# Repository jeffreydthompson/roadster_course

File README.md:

# Open Roadster

An open source remote control car you can build from scratch. The chassis, circuit board, firmware, and phone app are all here.

## What's inside

| | Folder | What you'll find |
|---|---|---|
| **Mechanical** | [`mechanical/`](mechanical/) | Chassis, steering and wheels in FreeCAD, ready-to-print STLs, a sheet metal base, and a Blender body |
| **Circuits** | [`circuits/`](circuits/) | A 4-layer ESP32-S3 controller board in KiCad, with order-ready files for JLCPCB |
| **Firmware** | [`code/firmware/`](code/firmware/) | Arduino firmware for motors, steering, lights, battery monitoring and Bluetooth LE |
| **App** | [`code/app/`](code/app/) | An iOS remote: tilt to steer, with throttle, gears, headlights and a fuel gauge |

Each folder has its own README with the details.

## The car at a glance

- **Brains:** ESP32-S3 on a custom 60 × 40 mm board
- **Drive:** two N20 gear motors, one per rear wheel
- **Steering:** micro servo with a steering linkage
- **Power:** single-cell LiPo, charged over USB-C, with a fuel gauge
- **Lights:** headlights, plus tail lights that double as brake lights
- **Control:** Bluetooth LE from your phone

## Building one

1. **Order the circuit board.** See [circuits](circuits/).
2. **Make the parts:** print the STLs, have the sheet metal base cut, and buy the motors, servo and bearings. See [mechanical](mechanical/).
3. **Flash the firmware** over USB-C. See [firmware](code/firmware/).
4. **Install the app** on your phone and drive. See [app](code/app/).

## Next steps

**A soft power switch.** Right now the car is turned on and off with a plain mechanical power switch. If it's left on, it keeps drawing current until the LiPo is run flat. Over-discharging a LiPo ruins it, and a damaged cell is a fire risk the next time it's charged.

The next board revision will add a soft switch: a push button that turns the car on, with power held on by the microcontroller. The firmware can then cut power completely, for example after a period of inactivity or when the battery gets low. That way the car can never be accidentally left on to drain the battery.

Other work in progress and known issues are tracked in [TODO.md](TODO.md).

## License

- Code (`code/`): [MIT](LICENSE)
- Hardware and mechanical designs (`mechanical/`, `circuits/`): [CC BY 4.0](https://creativecommons.org/licenses/by/4.0/)

See [LICENSE](LICENSE) for details.

The [Open Source Hardware logo](https://oshwa.org/resources/open-source-hardware-logo/) was designed by Macklin Chaffee and is used under a CC-SA license. Open Roadster is not OSHWA certified.

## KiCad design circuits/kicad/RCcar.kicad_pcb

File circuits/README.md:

# Circuits

The Open Roadster's controller: a 4-layer, 60 × 40 mm board built around an **ESP32-S3-MINI-1-N8**. It drives the motors, steering and lights, charges and monitors the battery, and talks to the phone over Bluetooth LE.

| Function | Part |
|---|---|
| Microcontroller (Wi-Fi + BLE) | ESP32-S3-MINI-1-N8 |
| Motor drivers (one per rear wheel) | 2× DRV8833 |
| Battery charger (single-cell LiPo, via USB-C) | MCP73831 |
| Fuel gauge | MAX17048 |
| 3.3 V supply (buck-boost) | TPS63001 |
| USB / battery power switchover | TPS2116 |
| USB-to-serial for programming | CP2102N |
| Connectors | USB-C, battery (PH2.0), 2× motor, servo, front + rear LED |

## What's here

```
circuits/
├── RCcar_schematic.pdf     # all schematic sheets, no software needed
├── kicad/                  # KiCad 10 project (schematic + PCB), where the design is maintained
├── fabrication/            # Gerbers, BOM, pick-and-place for JLCPCB (from KiCad)
└── easyeda/                # original EasyEDA Standard source (schematic + PCB)
    └── fabrication/        # archived order files exported from EasyEDA
```

- **Just looking?** Open `RCcar_schematic.pdf`. It has every sheet: Sheet 1, Power, Motor Control, LED Drivers, USB Programmer.
- **Editing the design?** Open `kicad/RCcar.kicad_pro` in [KiCad](https://www.kicad.org/) 10.
- **Ordering boards?** Use the files in `fabrication/` (see below).
- **Prefer EasyEDA?** In EasyEDA Standard, use **File → Open → EasyEDA Source** to open `easyeda/RCcar_schematic.json` and `easyeda/RCcar_pcb.json`.

## Ordering from JLCPCB

`fabrication/` has the order files in JLCPCB's format:

- `RCcar_kicad_gerber.zip`: upload this for bare boards (4 layers, 60 × 40 mm)
- `RCcar_bom_jlcpcb.csv` and `RCcar_cpl_jlcpcb.csv`: add these for assembly. Every part has an LCSC part number

Parts are on both sides, so choose two-sided assembly. Always check part rotations in JLCPCB's assembly preview before paying.

The original boards were made from the EasyEDA order files in `easyeda/fabrication/`, which are kept for reference. The KiCad set was checked against them:

- the same 91 parts with the same LCSC numbers
- identical positions, sides and rotations
- copper within about 1% per layer (pour edges)

KiCad also opens the solder mask around the bare mounting and locating holes.

## About the KiCad port

The design started in EasyEDA. The KiCad project was imported from the EasyEDA source and checked against it:

- Schematic and board agree on every connection. KiCad's schematic parity check finds no split or merged nets; the remaining parity notes are naming differences from the import.
- Design rules match EasyEDA's (0.152 mm minimum clearance, 0.254 mm tracks). DRC reports no clearance errors and no unconnected items.
- KiCad fills copper pours slightly differently from EasyEDA, so 14 short tracks (0.2 mm) were added where KiCad's fill couldn't reach a few fine-pitch pins that EasyEDA's pour connected (around U1, U3, U5, U6, U7 and R2).
- KiCad's Gerbers match EasyEDA's copper to within about 1% per layer. The differences are pour edges and thermal spokes around pads.
- The project is self-contained. All symbols and footprints live in project libraries (`RCcar.kicad_sym`, `RCcar.pretty/`), registered in the project's `sym-lib-table` and `fp-lib-table`.
- Remaining DRC/ERC items are left visible on purpose. They are cosmetic or come from the import:
  - courtyard overlaps from the tight placement
  - EasyEDA silkscreen touching pads
  - footprints that differ from their library copy by rounding or 3D model
  - EasyEDA symbols whose pin types trigger "not driven" and pin-type warnings
- 3D models aren't included yet, so the 3D viewer shows bare footprints.

The original EasyEDA board passes EasyEDA's design rule check with no errors, and all nets are routed.

## Known limitations

The board has no battery protection IC, so a pack left switched on can be run flat. See [TODO.md](../TODO.md) for the plan.

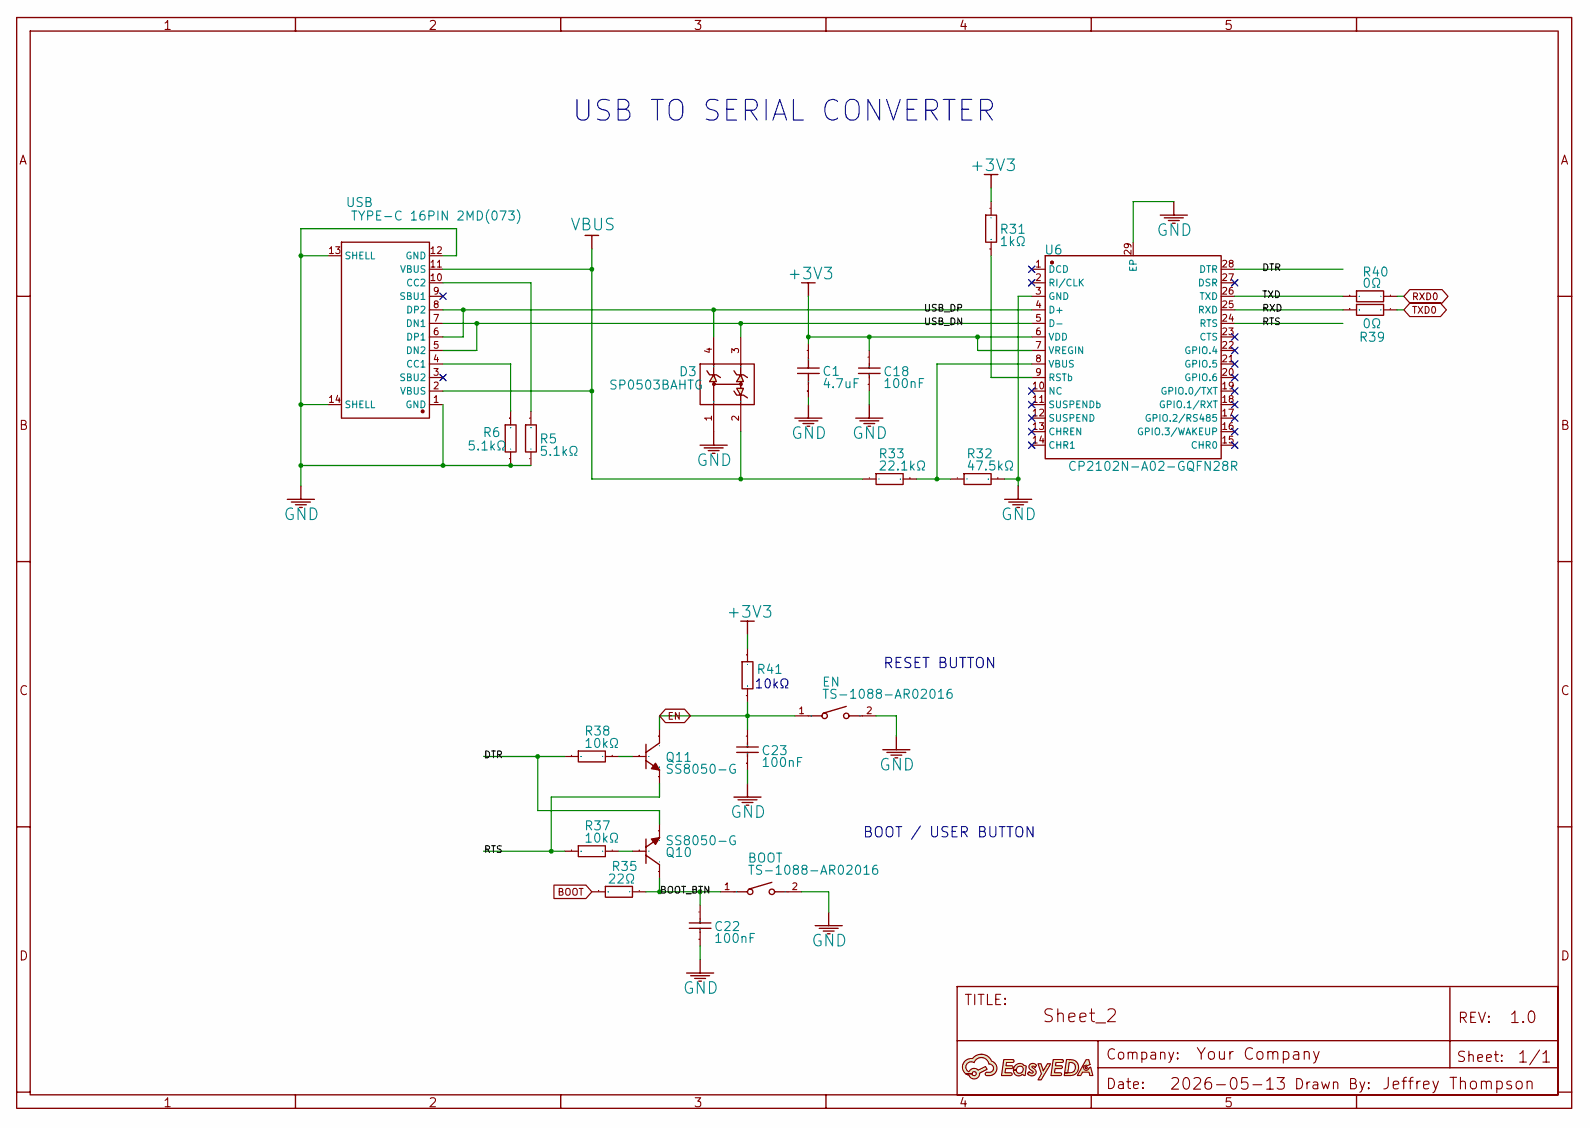
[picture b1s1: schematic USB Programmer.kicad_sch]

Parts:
A: A; Manufacturer Part ?
BOOT: TS-1088-AR02016; SW-SMD_L3.9-W3.0-P4.45; Manufacturer Part TS-1088-AR02016
C1: 4.7uF; C0402; Manufacturer Part CL05A475MP5NRNC
C18, C22, C23: 100nF; C0402_NEW; Manufacturer Part CL05B104KO5NNNC
D3: SP0503BAHTG; SOT-143_L2.9-W1.3-P1.92-LS2.3-BR; Manufacturer Part SP0503BAHTG
EN: TS-1088-AR02016; SW-SMD_L3.9-W3.0-P4.45; Manufacturer Part TS-1088-AR02016
Q10, Q11: SS8050-G; SOT-23-3_L2.9-W1.6-P1.90-LS2.8-BR; Manufacturer Part SS8050-G
R5, R6: 5.1kΩ; R0402; Manufacturer Part 0402WGF5101TCE
R31: 1kΩ; R0402; Manufacturer Part 0402WGF1001TCE
R32: 47.5kΩ; R0402; Manufacturer Part 0402WGF4752TCE
R33: 22.1kΩ; R0402; Manufacturer Part 0402WGF2212TCE
R35: 22Ω; R0402; Manufacturer Part 0402WGF220JTCE
R37, R38, R41: 10kΩ; R0402; Manufacturer Part 0402WGF1002TCE
R39, R40: 0Ω; R0402; Manufacturer Part 0402WGF0000TCE
U6: CP2102N-A02-GQFN28R; QFN-28_L5.0-W5.0-P0.50-TL-EP3.3; Manufacturer Part CP2102N-A02-GQFN28R
USB: TYPE-C 16PIN 2MD(073); USB-C-SMD_TYPE-C-6PIN-2MD-073; Manufacturer Part TYPE-C 16PIN 2MD(073)

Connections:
+3V3: C1.2, C18.2, R31.2, R41.2, U6.6 (VDD), U6.7 (VREGIN); also elsewhere on the board
/USB Programmer/BOOT_BTN: BOOT.1, C22.2, Q10.3 (C), R35.2
/USB Programmer/DTR: Q10.2 (E), R38.1, U6.28 (DTR)
/USB Programmer/RTS: Q11.2 (E), R37.1, U6.24 (RTS)
/USB Programmer/RXD: R39.1, U6.25 (RXD)
/USB Programmer/TXD: R40.1, U6.26 (TXD)
/USB Programmer/USB_DN: D3.3, U6.5 (D-), USB.5 (DN2), USB.7 (DN1)
/USB Programmer/USB_DP: D3.4, U6.4 (D+), USB.6 (DP1), USB.8 (DP2)
BOOT: R35.1; also elsewhere on the board
EN: C23.2, EN.1, Q11.3 (C), R41.1; also elsewhere on the board
GND: BOOT.2, C1.1, C18.1, C22.1, C23.1, D3.1, EN.2, R5.2, R6.2, R32.1, U6.3 (GND), U6.29 (EP), USB.1 (GND), USB.12 (GND), USB.13 (SHELL), USB.14 (SHELL); also elsewhere on the board
unnamed: Q10.1 (B), R37.2
unnamed: Q11.1 (B), R38.2
unnamed: R31.1, U6.9 (RSTb)
unnamed: R32.2, R33.1, U6.8 (VBUS)
unnamed: R6.1, USB.4 (CC1)
unnamed: R5.1, USB.10 (CC2)
RXD0: R40.2; also elsewhere on the board
TXD0: R39.2; also elsewhere on the board
VBUS: D3.2, R33.2, USB.2 (VBUS), USB.11 (VBUS); also elsewhere on the board

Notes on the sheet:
RESET BUTTON
10kΩ
BOOT / USER BUTTON
USB TO SERIAL CONVERTER

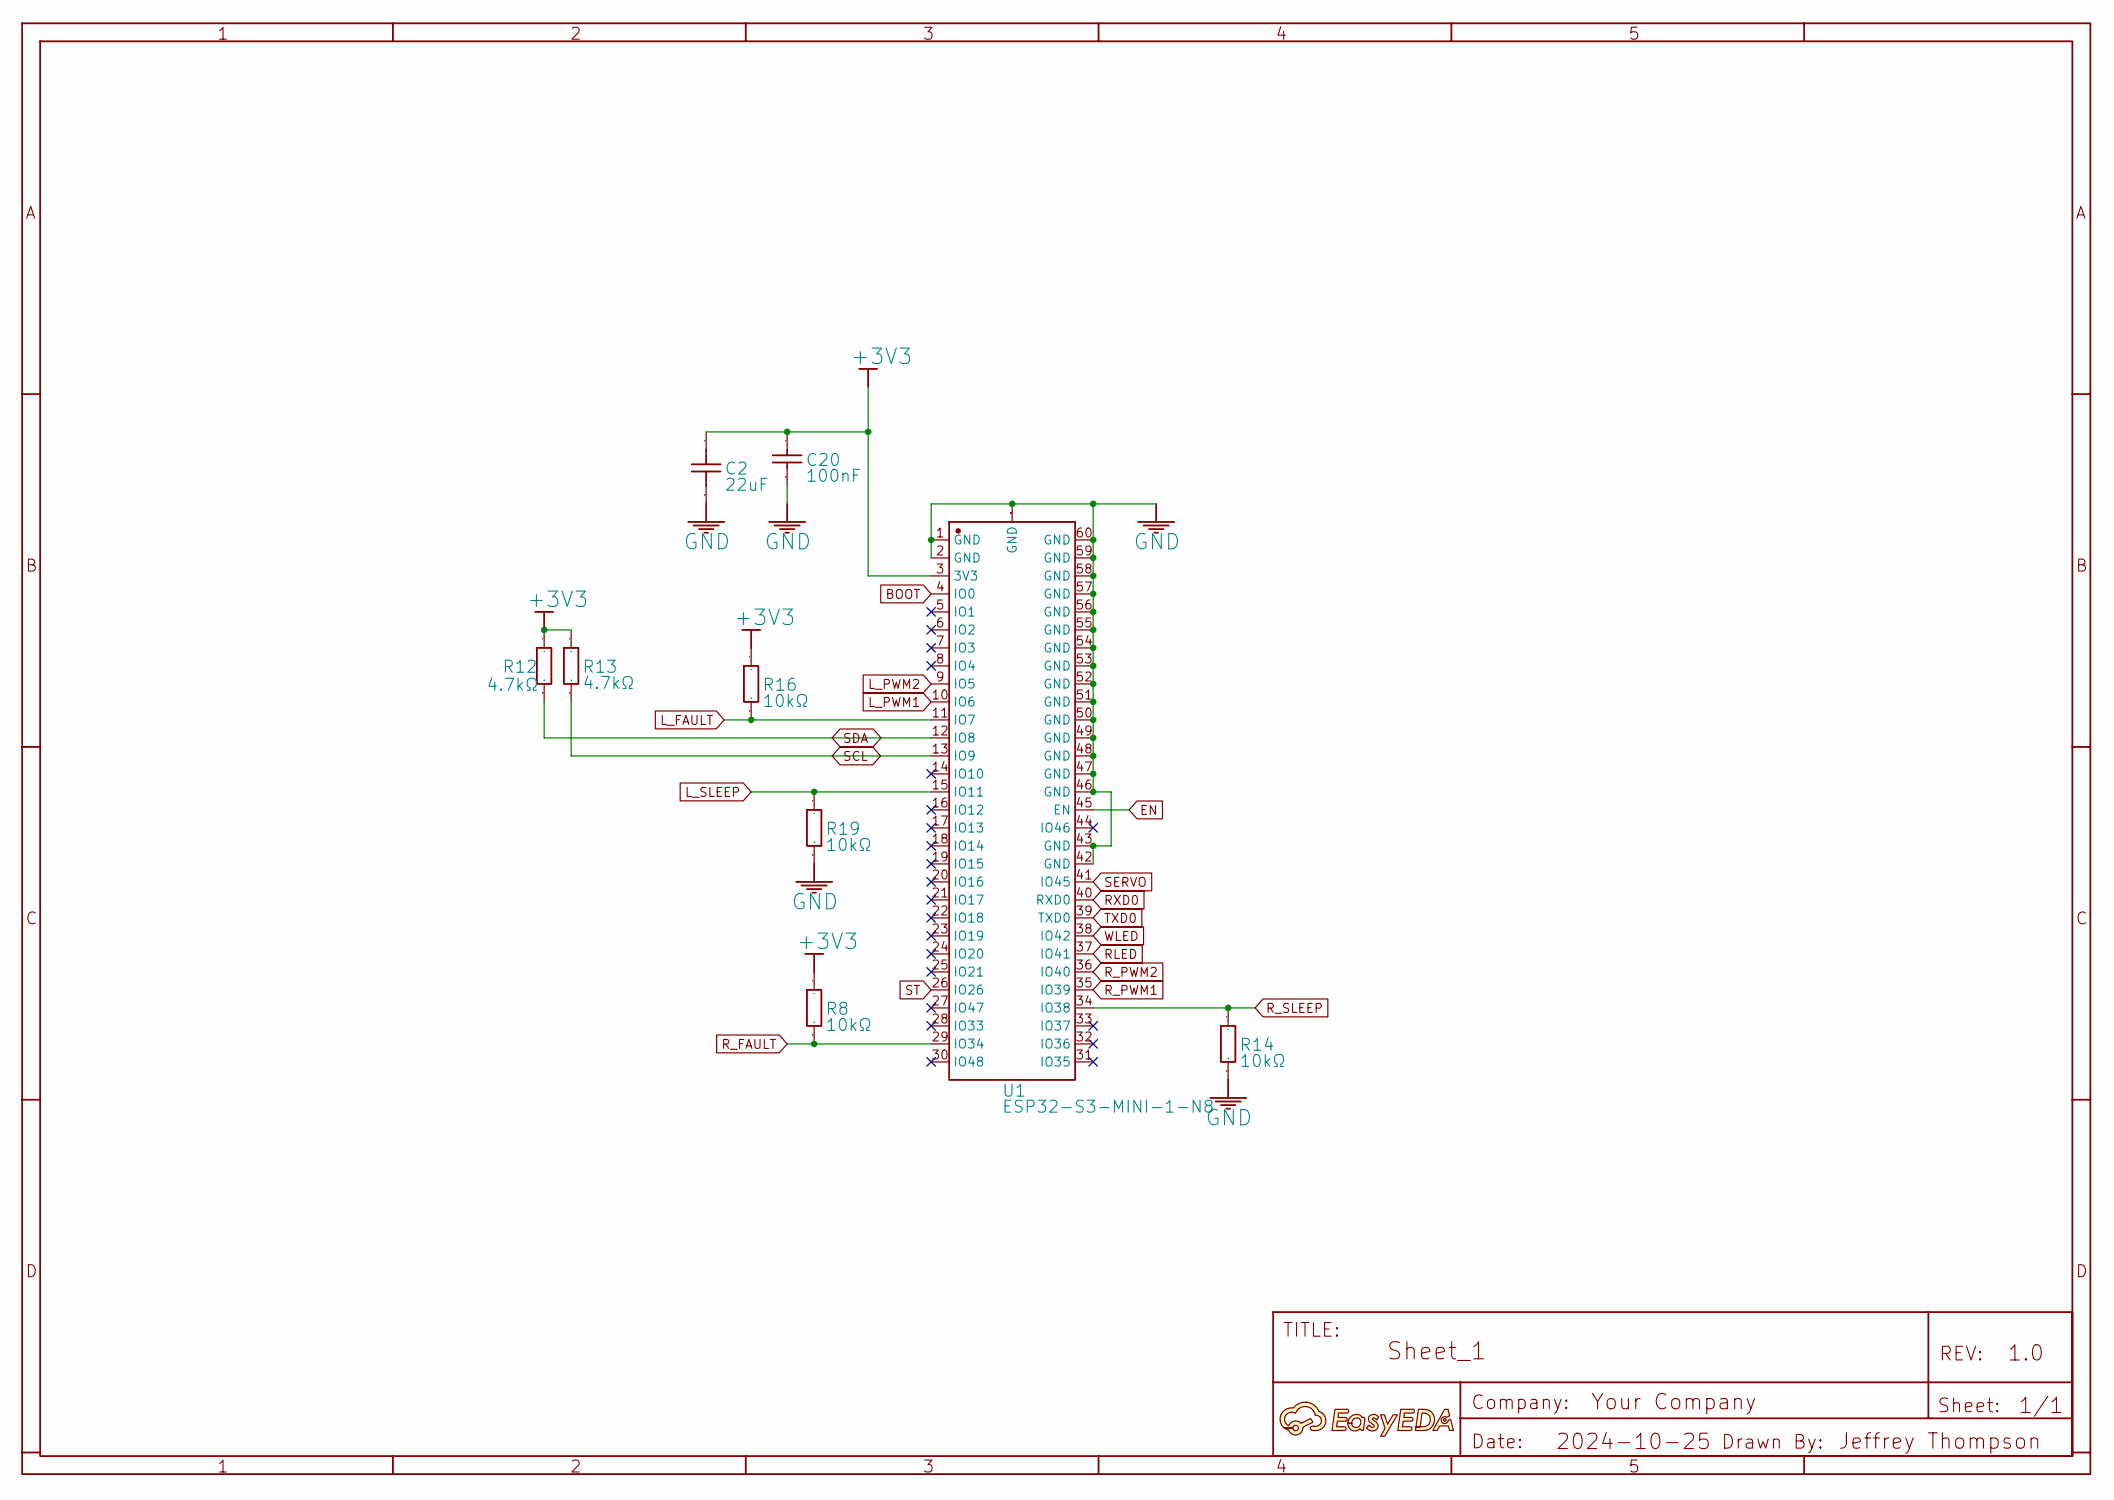
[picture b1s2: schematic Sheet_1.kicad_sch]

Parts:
A: A; Manufacturer Part ?
C2: 22uF; C0805; Manufacturer Part CL21A226MAQNNNE
C20: 100nF; C0402_NEW; Manufacturer Part CL05B104KO5NNNC
R8, R14, R16, R19: 10kΩ; R0402; Manufacturer Part 0402WGF1002TCE
R12, R13: 4.7kΩ; R0402; Manufacturer Part 0402WGF4701TCE
U1: ESP32-S3-MINI-1-N8; BULETM-SMD_ESP32-S3-MINI-1-N8; Manufacturer Part ESP32-S3-MINI-1-N8

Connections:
+3V3: C2.2, C20.2, R8.2, R12.2, R13.2, R16.2, U1.3 (3V3); also elsewhere on the board
BOOT: U1.4 (IO0); also elsewhere on the board
EN: U1.45 (EN); also elsewhere on the board
GND: C2.1, C20.1, R14.1, R19.1, U1.1 (GND), U1.2 (GND), U1.42 (GND), U1.43 (GND), U1.46 (GND), U1.47 (GND), U1.48 (GND), U1.49 (GND), U1.50 (GND), U1.51 (GND), U1.52 (GND), U1.53 (GND), U1.54 (GND), U1.55 (GND), U1.56 (GND), U1.57 (GND), U1.58 (GND), U1.59 (GND), U1.60 (GND), U1.GND; also elsewhere on the board
L_FAULT: R16.1, U1.11 (IO7); also elsewhere on the board
L_PWM1: U1.10 (IO6); also elsewhere on the board
L_PWM2: U1.9 (IO5); also elsewhere on the board
L_SLEEP: R19.2, U1.15 (IO11); also elsewhere on the board
RLED: U1.37 (IO41); also elsewhere on the board
RXD0: U1.40 (RXD0); also elsewhere on the board
R_FAULT: R8.1, U1.29 (IO34); also elsewhere on the board
R_PWM1: U1.35 (IO39); also elsewhere on the board
R_PWM2: U1.36 (IO40); also elsewhere on the board
R_SLEEP: R14.2, U1.34 (IO38); also elsewhere on the board
SCL: R13.1, U1.13 (IO9); also elsewhere on the board
SDA: R12.1, U1.12 (IO8); also elsewhere on the board
SERVO: U1.41 (IO45); also elsewhere on the board
ST: U1.26 (IO26); also elsewhere on the board
TXD0: U1.39 (TXD0); also elsewhere on the board
WLED: U1.38 (IO42); also elsewhere on the board

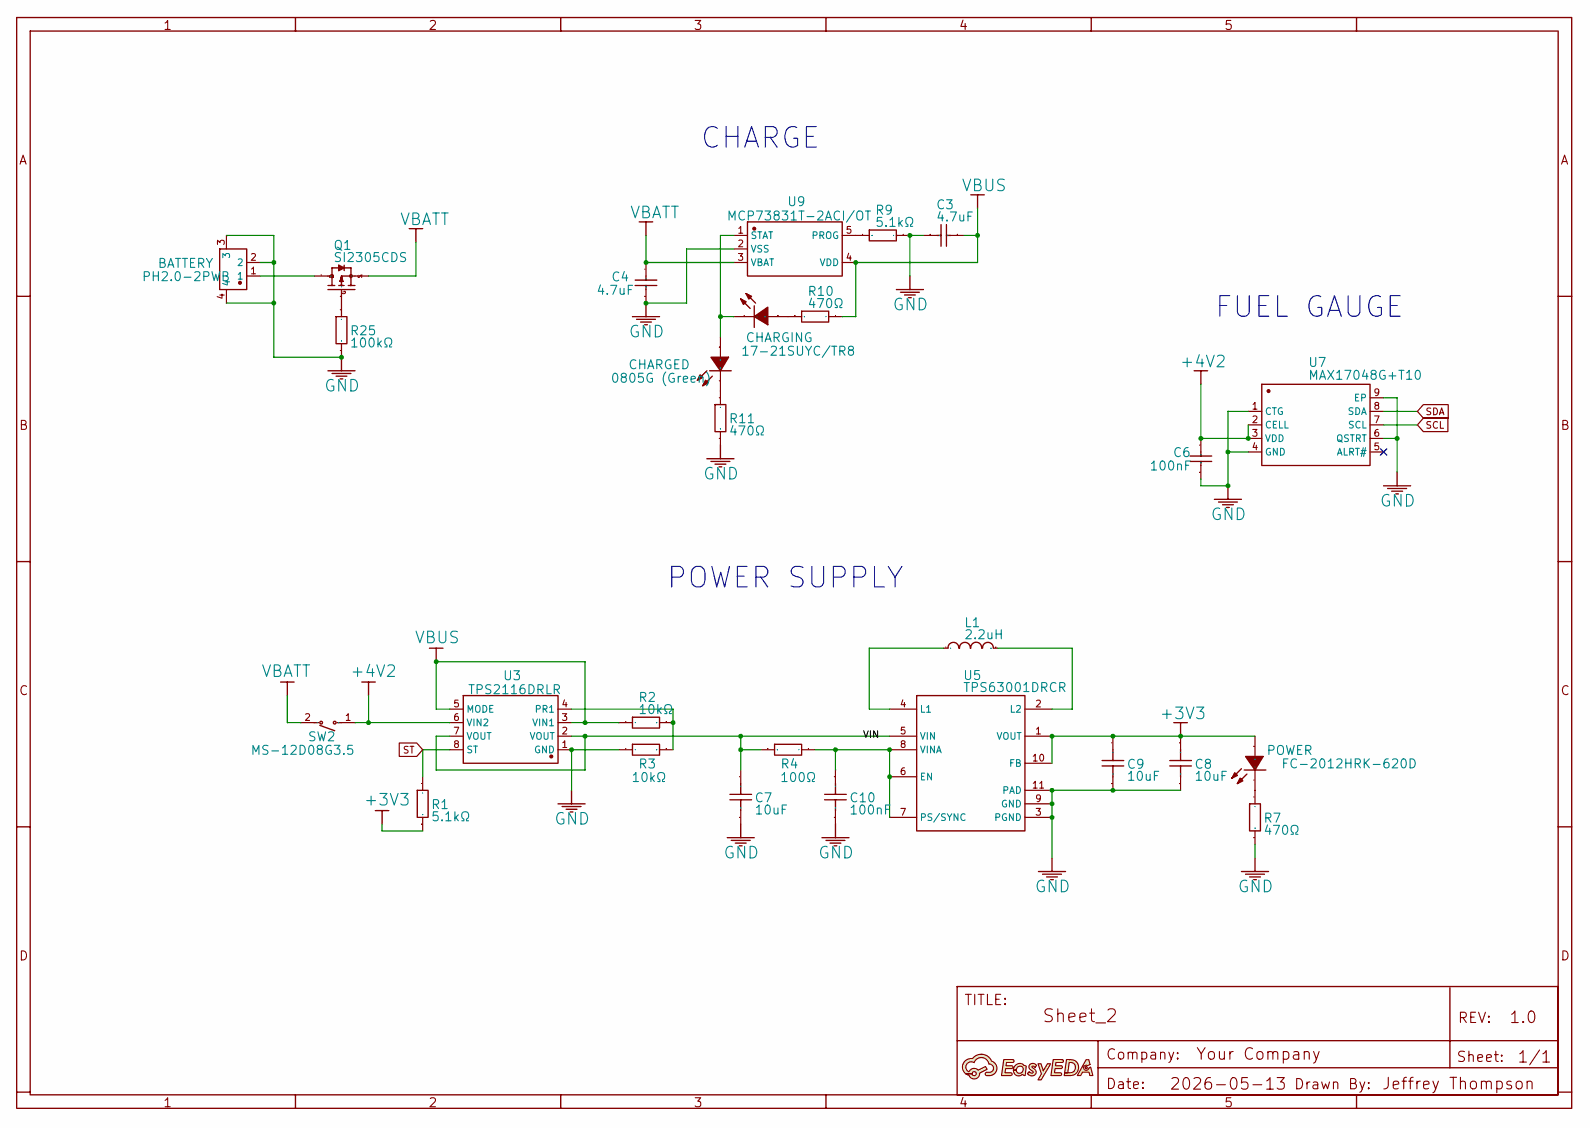
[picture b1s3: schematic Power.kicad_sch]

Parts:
A: A; Manufacturer Part ?
BATTERY: PH2.0-2PWB; CONN-SMD_2P-P2.00_PH2.0-SPWB; Manufacturer Part PH-2P卧贴
C3, C4: 4.7uF; C0805; Manufacturer Part CL21A475KAQNNNE
C6: 100nF; C0402_NEW; Manufacturer Part CL05B104KO5NNNC
C7, C8, C9: 10uF; C0603; Manufacturer Part CL10B106MQ8NRNC
C10: 100nF; C0402_v2; Manufacturer Part CL05B104KO5NNNC
CHARGED: 0805G (Green); LED0805-R-RD; Manufacturer Part KT-0805G
CHARGING: 17-21SUYC/TR8; LED0805-R-RD; Manufacturer Part KT-0805黄灯
L1: 2.2uH; IND-SMD_L3.0-W3.0_FNR30XXS; Manufacturer Part SPH3015H2R2MT
POWER: FC-2012HRK-620D; LED0805-R-RD; Manufacturer Part NCD0805R1
Q1: SI2305CDS; SOT-23-3_L2.9-W1.6-P1.90-LS2.8-BR; Manufacturer Part SI2305CDS
R1, R9: 5.1kΩ; R0402; Manufacturer Part 0402WGF5101TCE
R2, R3: 10kΩ; R0402; Manufacturer Part 0402WGF1002TCE
R4: 100Ω; R0402; Manufacturer Part 0402WGF1000TCE
R7, R10, R11: 470Ω; R0603; Manufacturer Part 0603WAF4700T5E
R25: 100kΩ; R0603; Manufacturer Part 0603WAF1003T5E
SW2: MS-12D08G3.5; SW-TH_MS-12D08G3.5; Manufacturer Part MS-12D08G3.5
U3: TPS2116DRLR; SOT-583-8_L2.1-W1.6-P0.50-LS1.6-BL; Manufacturer Part TPS2116DRLR
U5: TPS63001DRCR; VSON-10_L3.0-W3.0-P0.50-TL-EP_TPS62410DRCR; Manufacturer Part TPS63001DRCR
U7: MAX17048G+T10; TDFN-8_L2.0-W2.0-P0.50-BL-EP1.2; Manufacturer Part MAX17048G+T10
U9: MCP73831T-2ACI/OT; SOT-23-5_L3.0-W1.7-P0.95-LS2.8-BR; Manufacturer Part MCP73831T-2ACI/OT

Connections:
+3V3: C8.2, C9.2, POWER.1 (+), R1.1, U5.1 (VOUT), U5.10 (FB); also elsewhere on the board
+4V2: C6.2, SW2.1, U3.6 (VIN2), U7.2 (CELL), U7.3 (VDD); also elsewhere on the board
/Power/VIN: C7.2, R4.1, U3.2 (VOUT), U3.7 (VOUT), U5.5 (VIN)
GND: BATTERY.2, BATTERY.3, BATTERY.4, C3.1, C4.1, C6.1, C7.1, C8.1, C9.1, C10.1, R3.2, R7.1, R9.2, R11.1, R25.1, U3.1 (GND), U5.3 (PGND), U5.9 (GND), U5.11 (PAD), U7.1 (CTG), U7.4 (GND), U7.6 (QSTRT), U7.9 (EP), U9.2 (VSS); also elsewhere on the board
unnamed: CHARGED.1 (A), CHARGING.2 (-), U9.1 (STAT)
unnamed: CHARGED.2 (K), R11.2
unnamed: CHARGING.1 (+), R10.1
unnamed: POWER.2 (-), R7.2
unnamed: BATTERY.1, Q1.3 (D)
unnamed: Q1.1 (G), R25.2
unnamed: R2.1, R3.1, U3.4 (PR1)
unnamed: C10.2, R4.2, U5.6 (EN), U5.7 (PS/SYNC), U5.8 (VINA)
unnamed: L1.2, U5.4 (L1)
unnamed: L1.1, U5.2 (L2)
unnamed: R9.1, U9.5 (PROG)
SCL: U7.7 (SCL); also elsewhere on the board
SDA: U7.8 (SDA); also elsewhere on the board
ST: R1.2, U3.8 (ST); also elsewhere on the board
VBATT: C4.2, Q1.2 (S), SW2.2, U9.3 (VBAT)
VBUS: C3.2, R2.2, R10.2, U3.3 (VIN1), U3.5 (MODE), U9.4 (VDD); also elsewhere on the board

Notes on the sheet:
FUEL GAUGE
POWER SUPPLY
CHARGE

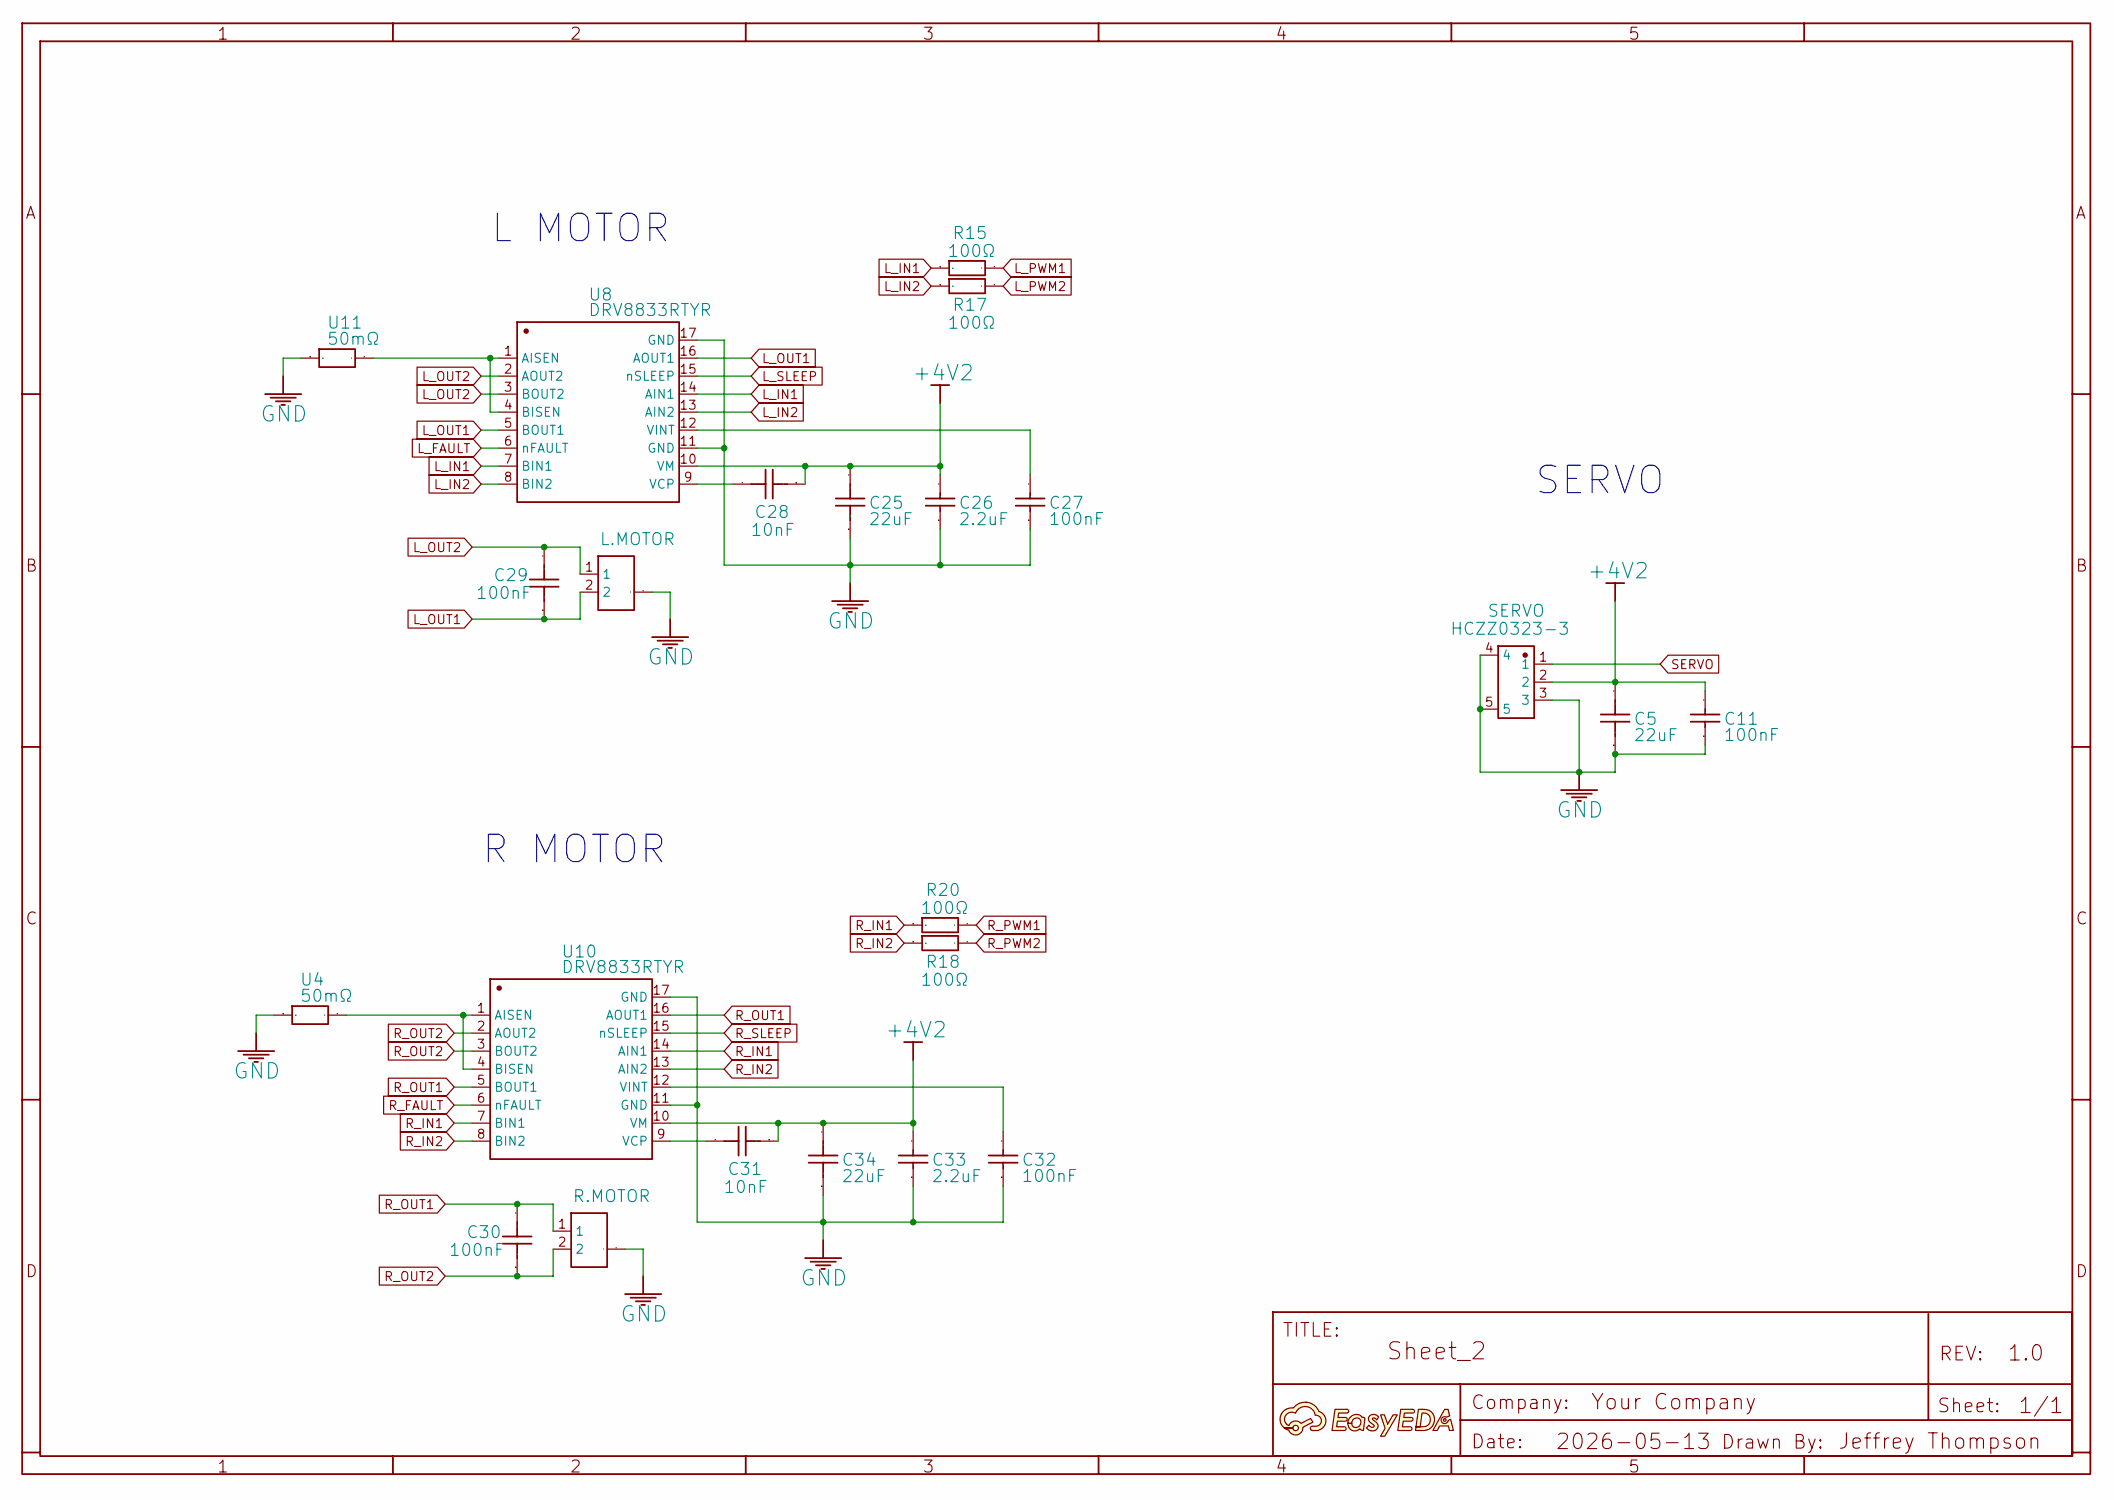
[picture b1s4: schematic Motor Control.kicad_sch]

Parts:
A: A; Manufacturer Part ?
C5, C25, C34: 22uF; C1206; Manufacturer Part HGC1206R7226K160NSPJ
C11, C27, C32: 100nF; C0603; Manufacturer Part CL10B104KO8NNNC
C26, C33: 2.2uF; C0603; Manufacturer Part CL10B225KP8NNNC
C28, C31: 10nF; C0603; Manufacturer Part CC0603KRX7R7BB103
C29, C30: 100nF; C0603; Manufacturer Part CC0603KRX7R9BB104
L.MOTOR: S2B-ZR-SM4A-TF(LF)(SN); CONN-SMD_S2B-ZR-SM4A; Manufacturer Part S2B-ZR-SM4A-TF(LF)(SN)
R15, R17, R18, R20: 100Ω; R0402; Manufacturer Part RC0402FR-07100RL
R.MOTOR: S2B-ZR-SM4A-TF(LF)(SN); CONN-SMD_S2B-ZR-SM4A; Manufacturer Part S2B-ZR-SM4A-TF(LF)(SN)
SERVO: HCZZ0323-3; CONN-SMD_3P-P1.50_HCZZ0323-3; Manufacturer Part HCZZ0323-3
U4, U11: 50mΩ; R1206; Manufacturer Part FRM121WFR050TM
U8, U10: DRV8833RTYR; QFN-16_L4.0-W4.0-P0.65-TL-EP2.6; Manufacturer Part DRV8833RTYR

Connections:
+4V2: C5.2, C11.2, C25.2, C26.2, C28.1, C31.1, C33.2, C34.2, SERVO.2, U8.10 (VM), U10.10 (VM); also elsewhere on the board
GND: C5.1, C11.1, C25.1, C26.1, C27.1, C32.1, C33.1, C34.1, L.MOTOR.0, R.MOTOR.0, SERVO.3, SERVO.4, SERVO.5, U4.1, U8.11 (GND), U8.17 (GND), U10.11 (GND), U10.17 (GND), U11.1; also elsewhere on the board
L_FAULT: U8.6 (nFAULT); also elsewhere on the board
L_IN1: R15.1, U8.7 (BIN1), U8.14 (AIN1)
L_IN2: R17.1, U8.8 (BIN2), U8.13 (AIN2)
L_OUT1: C29.1, L.MOTOR.2, U8.5 (BOUT1), U8.16 (AOUT1)
L_OUT2: C29.2, L.MOTOR.1, U8.2 (AOUT2), U8.3 (BOUT2)
L_PWM1: R15.2; also elsewhere on the board
L_PWM2: R17.2; also elsewhere on the board
L_SLEEP: U8.15 (nSLEEP); also elsewhere on the board
unnamed: U8.1 (AISEN), U8.4 (BISEN), U11.2
unnamed: C28.2, U8.9 (VCP)
unnamed: C27.2, U8.12 (VINT)
unnamed: U4.2, U10.1 (AISEN), U10.4 (BISEN)
unnamed: C31.2, U10.9 (VCP)
unnamed: C32.2, U10.12 (VINT)
R_FAULT: U10.6 (nFAULT); also elsewhere on the board
R_IN1: R20.1, U10.7 (BIN1), U10.14 (AIN1)
R_IN2: R18.1, U10.8 (BIN2), U10.13 (AIN2)
R_OUT1: C30.2, R.MOTOR.1, U10.5 (BOUT1), U10.16 (AOUT1)
R_OUT2: C30.1, R.MOTOR.2, U10.2 (AOUT2), U10.3 (BOUT2)
R_PWM1: R20.2; also elsewhere on the board
R_PWM2: R18.2; also elsewhere on the board
R_SLEEP: U10.15 (nSLEEP); also elsewhere on the board
SERVO: SERVO.1; also elsewhere on the board

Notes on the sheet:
SERVO
R MOTOR
L MOTOR

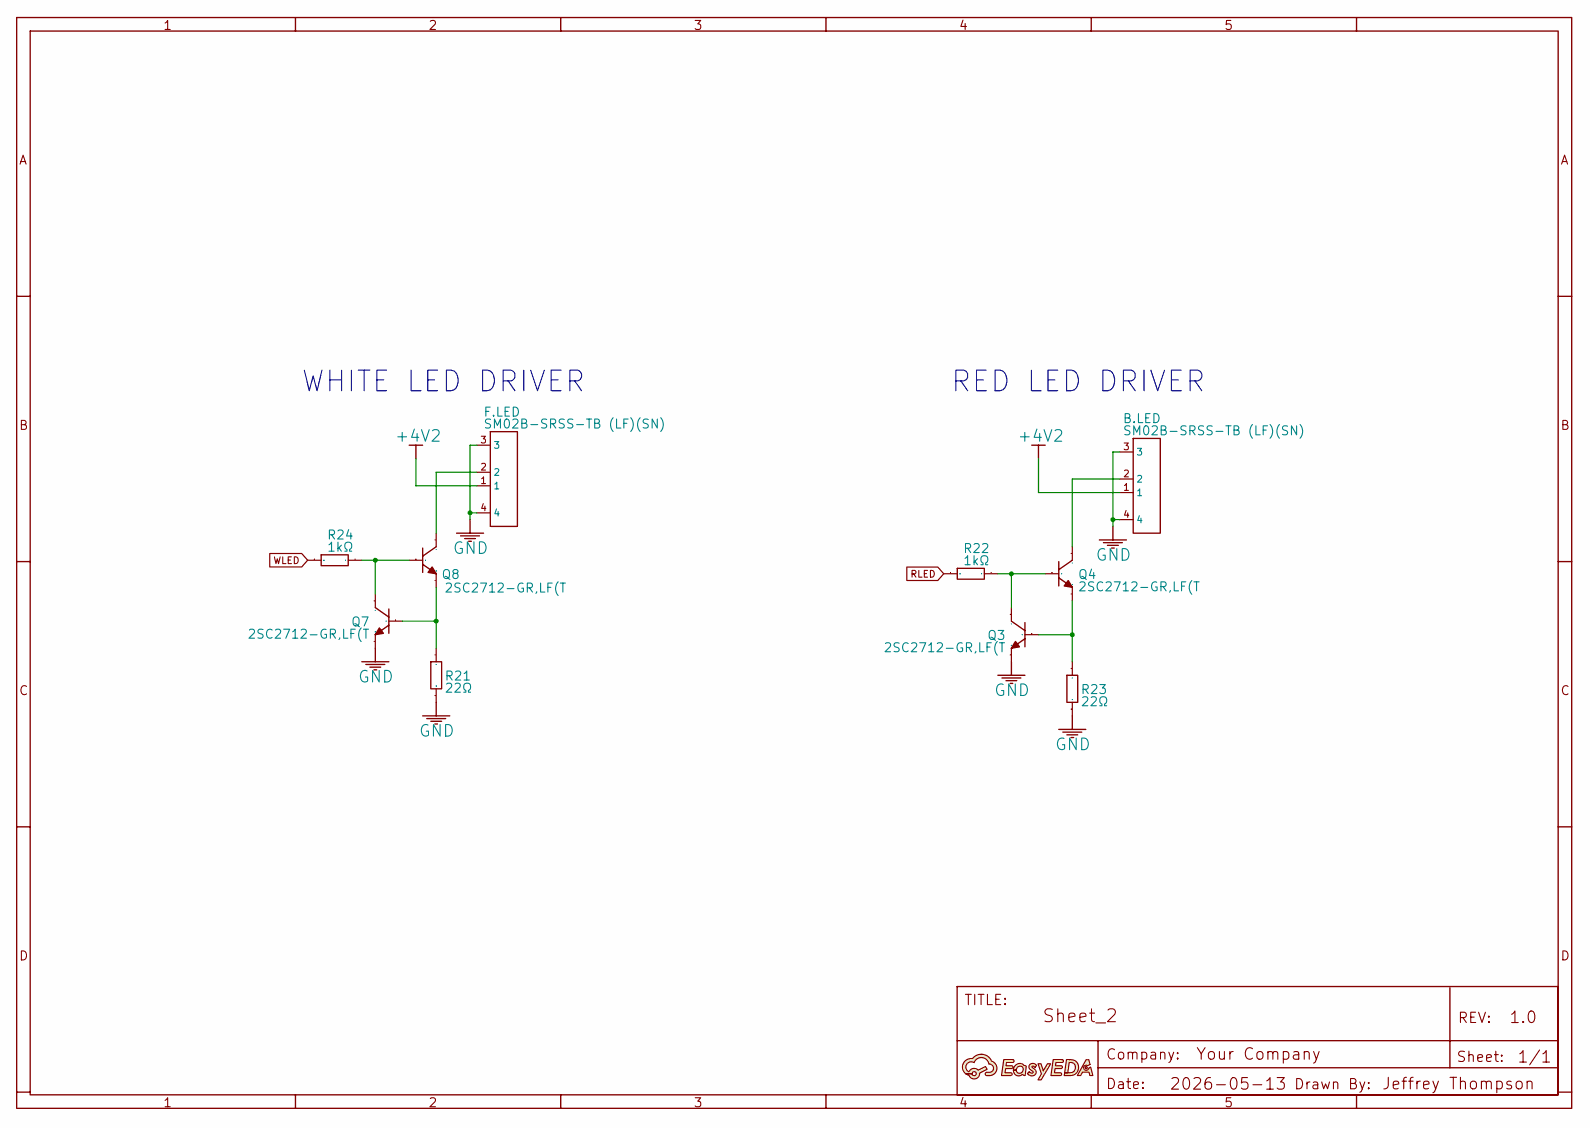
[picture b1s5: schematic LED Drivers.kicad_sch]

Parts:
A: A; Manufacturer Part ?
B.LED: SM02B-SRSS-TB (LF)(SN); CONN-SMD_2P-P1.00_SM02B-SRSS-TB-LF-SN; Manufacturer Part SM02B-SRSS-TB(LF)(SN)
F.LED: SM02B-SRSS-TB (LF)(SN); CONN-SMD_2P-P1.00_SM02B-SRSS-TB-LF-SN; Manufacturer Part SM02B-SRSS-TB(LF)(SN)
Q3, Q4, Q7, Q8: 2SC2712-GR,LF(T; SOT-23-3_L2.9-W1.6-P1.90-LS2.8-BR; Manufacturer Part 2SC2712-GR,LF(T
R21, R23: 22Ω; R0603; Manufacturer Part 0603WAF220JT5E
R22, R24: 1kΩ; R0603; Manufacturer Part MCT06030C1001FP500

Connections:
+4V2: B.LED.1, F.LED.1; also elsewhere on the board
GND: B.LED.3, B.LED.4, F.LED.3, F.LED.4, Q3.2 (E), Q7.2 (E), R21.1, R23.1; also elsewhere on the board
unnamed: Q3.1 (B), Q4.2 (E), R23.2
unnamed: Q3.3 (C), Q4.1 (B), R22.2
unnamed: B.LED.2, Q4.3 (C)
unnamed: Q7.1 (B), Q8.2 (E), R21.2
unnamed: Q7.3 (C), Q8.1 (B), R24.2
unnamed: F.LED.2, Q8.3 (C)
RLED: R22.1; also elsewhere on the board
WLED: R24.1; also elsewhere on the board

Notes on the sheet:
RED LED DRIVER
WHITE LED DRIVER
